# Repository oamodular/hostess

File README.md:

# hostess
eurorack version of midi2usbhost [https://github.com/rppicomidi/midi2usbhost]

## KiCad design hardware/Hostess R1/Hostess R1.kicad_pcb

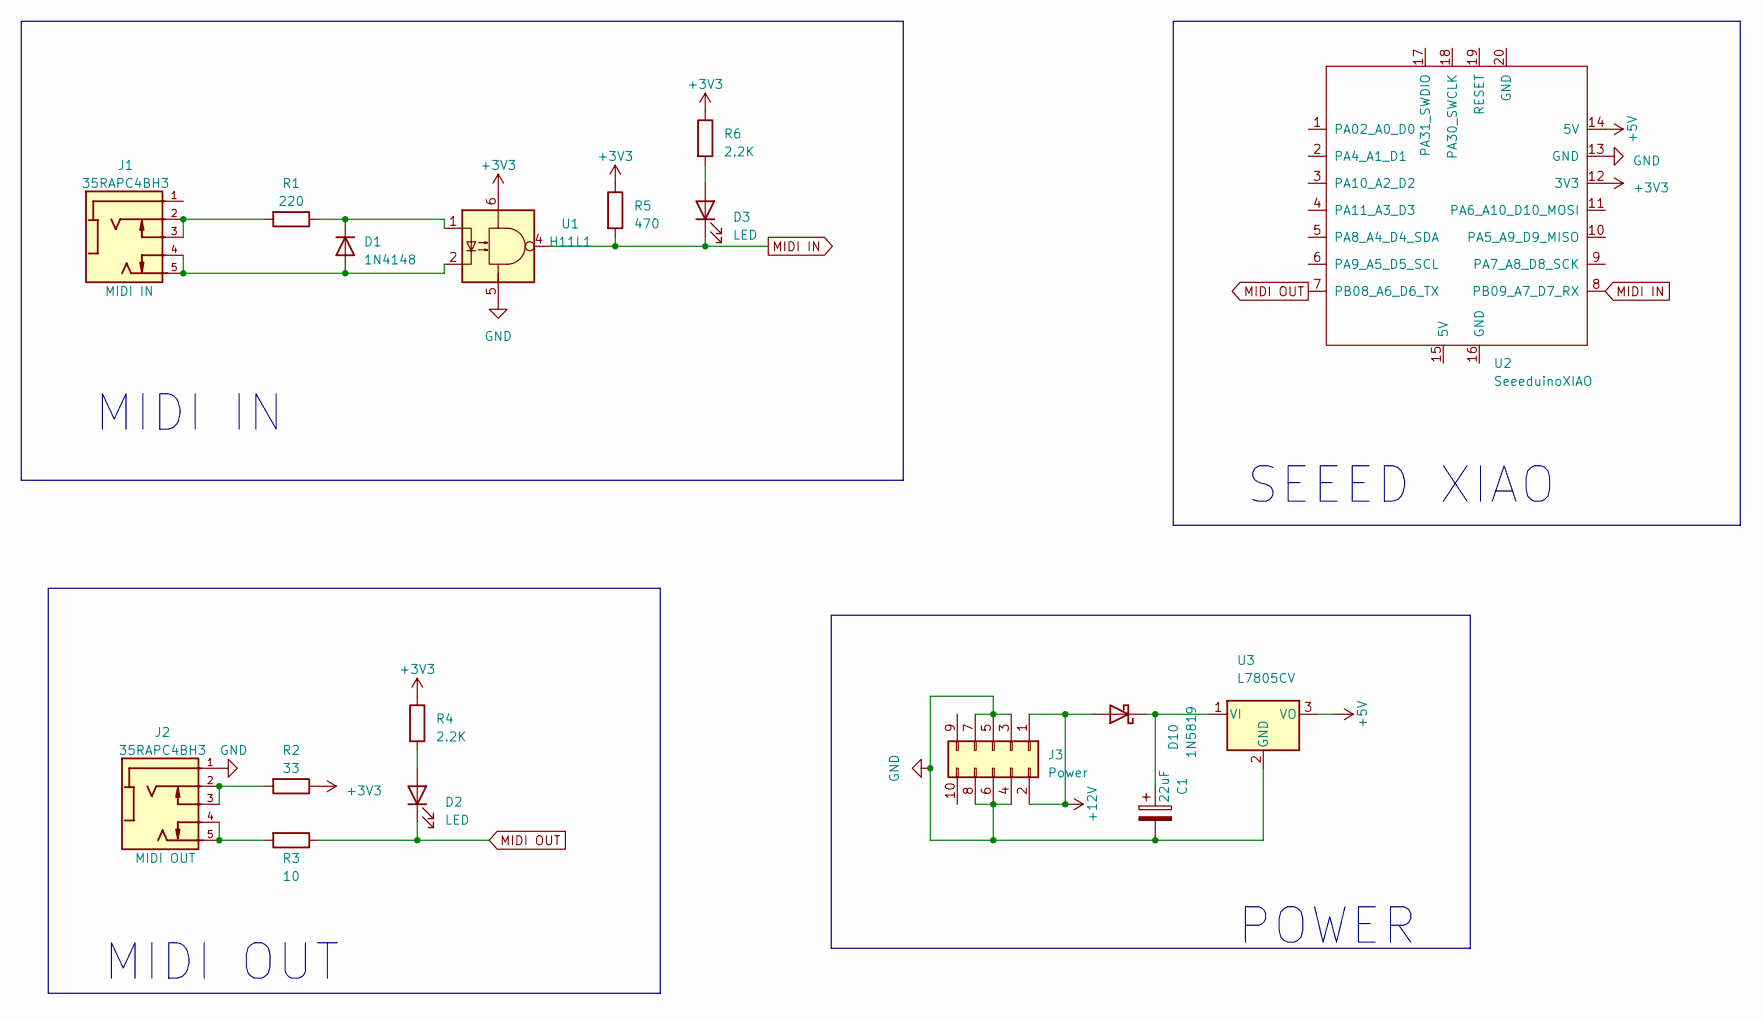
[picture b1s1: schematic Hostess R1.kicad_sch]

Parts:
C1: 22uF; CP_Radial_D5.0mm_P2.50mm
D1: 1N4148; D_DO-35_SOD27_P7.62mm_Horizontal
D2, D3: LED; LED_D3.0mm_Horizontal_O3.81mm_Z2.0mm
D10: 1N5819; D_DO-41_SOD81_P7.62mm_Horizontal
J1, J2: 35RAPC4BH3; Socket-Horizontal stereo 2-switch THT-SWITCHCRAFT_35RAPC4BH3
J3: Power; PinHeader_2x05_P2.54mm_Horizontal
R1: 220; Resistor-THT-Axial Horizontal pin pitch 7.62mm 0.25W
R2: 33; Resistor-THT-Axial Horizontal pin pitch 7.62mm 0.25W
R3: 10; Resistor-THT-Axial Horizontal pin pitch 7.62mm 0.25W
R4, R6: 2.2K; Resistor-THT-Axial Horizontal pin pitch 7.62mm 0.25W
R5: 470; Resistor-THT-Axial Horizontal pin pitch 7.62mm 0.25W
U1: H11L1; DIP-6_W7.62mm_LongPads
U2: SeeeduinoXIAO; Microcontroller-XIAO RP2040
U3: L7805CV; TO-220-3_Horizontal_TabDown

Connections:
+3V3: R2.1, R4.1, R5.1, R6.1, U1.6, U2.12 (3V3)
+5V: U2.14 (5V), U3.3 (VO)
+12V: J3.1, J3.2; also elsewhere on the board
GND: C1.2, J2.1, J3.3, J3.4, J3.5, J3.6, J3.7, J3.8, U1.5, U2.13 (GND), U3.2 (GND)
MIDI IN: D3.1 (K), R5.2, U1.4, U2.8 (PB09_A7_D7_RX)
MIDI OUT: D2.1 (K), R3.1, U2.7 (PB08_A6_D6_TX)
unnamed: D1.2 (A), J1.4, J1.5, U1.2
unnamed: D1.1 (K), R1.1, U1.1
unnamed: D2.2 (A), R4.2
unnamed: D3.2 (A), R6.2
unnamed 10: C1.1, U3.1 (VI); also elsewhere on the board
unnamed: J1.2, J1.3, R1.2
unnamed: J2.2, J2.3, R2.2
unnamed: J2.4, J2.5, R3.2

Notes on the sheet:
POWER
MIDI IN
SEEED XIAO
MIDI OUT

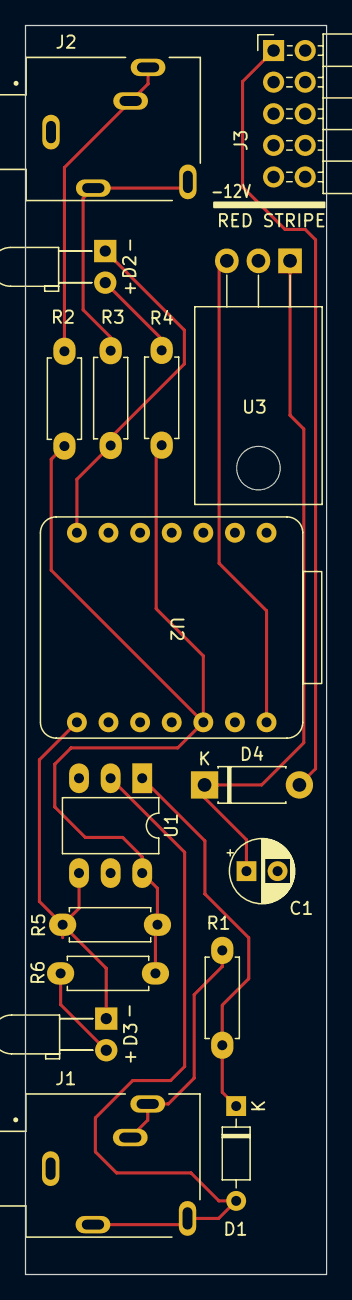
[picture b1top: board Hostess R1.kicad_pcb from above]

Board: 2 copper layers, 24.2 x 100.4 mm, 17 parts (0 on the bottom side), 14 nets.

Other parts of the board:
D4: 1N5819; D_DO-41_SOD81_P7.62mm_Horizontal

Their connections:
+12V: D4.2 (A); also elsewhere on the board
unnamed 10: D4.1 (K); also elsewhere on the board

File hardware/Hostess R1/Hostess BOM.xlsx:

Item # | Designator | Quantity | Manufacturer | Mfg Part # | Descripton / Value | Package / Footprint | Type
1 | D4 | 1 |  | 1N5819 |  | DO-41_SOD81_P7.62mm_Horizontal | THT
2 | R4,R6 | 2 |  |  | 2.2K | 7.62mm 0.25W | THT
3 | R1 | 1 |  |  | 220 ohm | 7.62mm 0.25W | THT
4 | R5 | 1 |  |  | 470 ohm | 7.62mm 0.25W | THT
5 | U2 | 1 | Seeed Studio |  | Seeed XIAO RP2040 microcontroller | THT | THT
6 | R2 | 1 |  |  | 33 ohm | 7.62mm 0.25W | THT
7 | R3 | 1 |  |  | 10 ohm | 7.62mm 0.25W | THT
8 | U1 | 1 |  | H11L1 |  | DIP-6_W7.62mm | THT
9 | D2,D3 | 2 | Optosupply | OSC84L3131A | 3mm LED baby pink | D3.0mm_Horizontal_O3.81mm_Z2.0mm | THT
10 | U3 | 1 |  | L7805CV |  | TO-220-3 | THT
11 | D1 | 1 |  | 1N4148 |  | DO-35_SOD27_P7.62mm_Horizontal | THT
12 | J1,J2 | 2 | Switchcraft | 35RAPC4BH3 | Horizontal stereo 2-switch sockets | THT | THT
13 | J3 | 1 |  |  | Right angle pin header 2x5 | 2x05 P2.54mm Horizontal | THT
14 | C1 | 1 |  |  | 22uF | CP_Radial_D5.0mm_P2.50mm | THT

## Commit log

2023-11-04 kicad for the first prototype
